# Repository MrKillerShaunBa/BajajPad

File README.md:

# BajajPad

A handy macropad with a rotary encoder and an OLED display. This is created for the Hack Club HackPad V3 YSWS.

### Inspiration

I looked at so many different projects which motivated me to try my hand at this.

### Challenges

I used 3D modelling and PCB software for the first time. It took a lot of time and a lot of Google searches to finally complete it. I faced a lot of problems in Fusion 360 particularly when aligning the case parts, PCB and keycaps for a test fit. 

Schematic            |  PCB         |   Case
:-------------------------:|:-------------------------:|:-------------------------:|
||

## BOM
- 11x Cherry MX Switches
- 1x XIAO RP2040
- 11x Blank DSA Keycaps
- 1x EC11 Rotary Encoder
- 1x 0.91 inch OLED display
- 4x M3x16 Bolt
- 4x M3 Heatset
- 1x Knob (if available)

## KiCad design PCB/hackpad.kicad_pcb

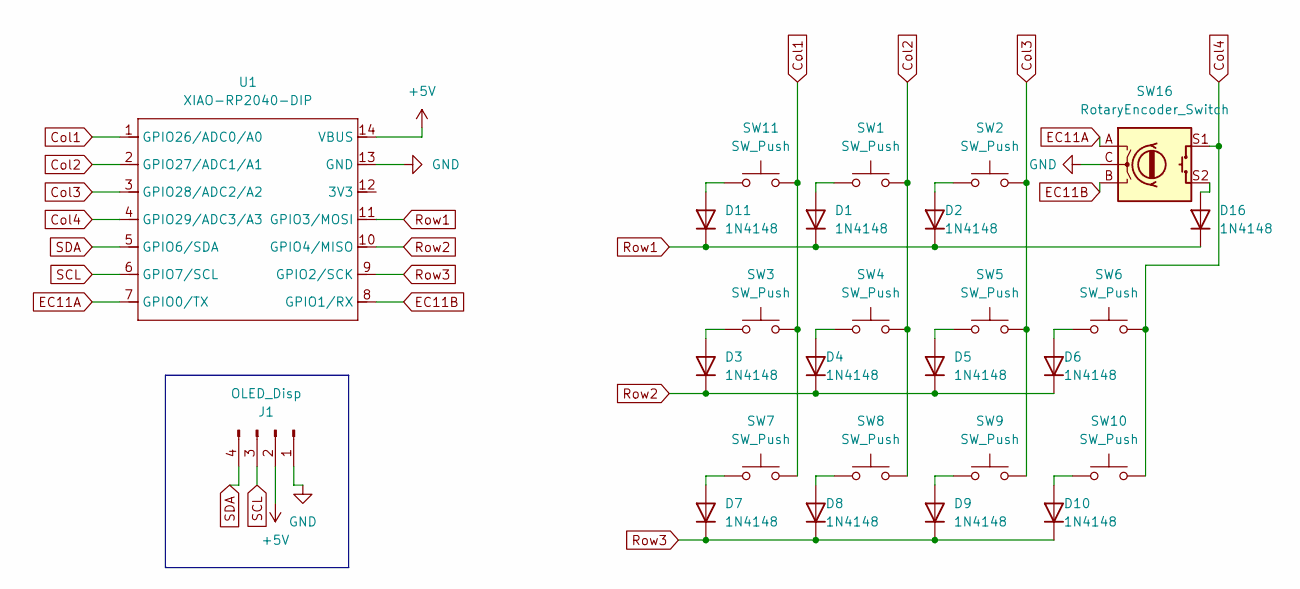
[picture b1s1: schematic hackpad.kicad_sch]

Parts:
D1, D2, D3, D4, D5, D6, D7, D8, D9, D10, D11, D16: 1N4148; D_DO-35_SOD27_P7.62mm_Horizontal
J1: OLED_Disp; SSD1306-0.91-OLED-4pin-128x32_3d
SW1, SW2, SW3, SW4, SW5, SW6, SW7, SW8, SW9, SW10, SW11: SW_Push; SW_Cherry_MX_1.00u_PCB_3D
SW16: RotaryEncoder_Switch; RotaryEncoder_Alps_EC11E-Switch_Vertical_H20mm_3d
U1: XIAO-RP2040-DIP; XIAO-RP2040-DIP_3d

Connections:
+5V: J1.2, U1.14 (VBUS)
Col1: SW3.2, SW7.2, SW11.2, U1.1 (GPIO26/ADC0/A0)
Col2: SW1.2, SW4.2, SW8.2, U1.2 (GPIO27/ADC1/A1)
Col3: SW2.2, SW5.2, SW9.2, U1.3 (GPIO28/ADC2/A2)
Col4: SW6.2, SW10.2, SW16.S1, U1.4 (GPIO29/ADC3/A3)
EC11A: SW16.A, U1.7 (GPIO0/TX)
EC11B: SW16.B, U1.8 (GPIO1/RX)
GND: J1.1, SW16.C, U1.13 (GND)
unnamed: D1.2 (A), SW1.1
unnamed: D2.2 (A), SW2.1
unnamed: D3.2 (A), SW3.1
unnamed: D4.2 (A), SW4.1
unnamed: D5.2 (A), SW5.1
unnamed: D6.2 (A), SW6.1
unnamed: D7.2 (A), SW7.1
unnamed: D8.2 (A), SW8.1
unnamed: D9.2 (A), SW9.1
unnamed: D10.2 (A), SW10.1
unnamed: D11.2 (A), SW11.1
unnamed: D16.2 (A), SW16.S2
Row1: D1.1 (K), D2.1 (K), D11.1 (K), D16.1 (K), U1.11 (GPIO3/MOSI)
Row2: D3.1 (K), D4.1 (K), D5.1 (K), D6.1 (K), U1.10 (GPIO4/MISO)
Row3: D7.1 (K), D8.1 (K), D9.1 (K), D10.1 (K), U1.9 (GPIO2/SCK)
SCL: J1.3, U1.6 (GPIO7/SCL)
SDA: J1.4, U1.5 (GPIO6/SDA)

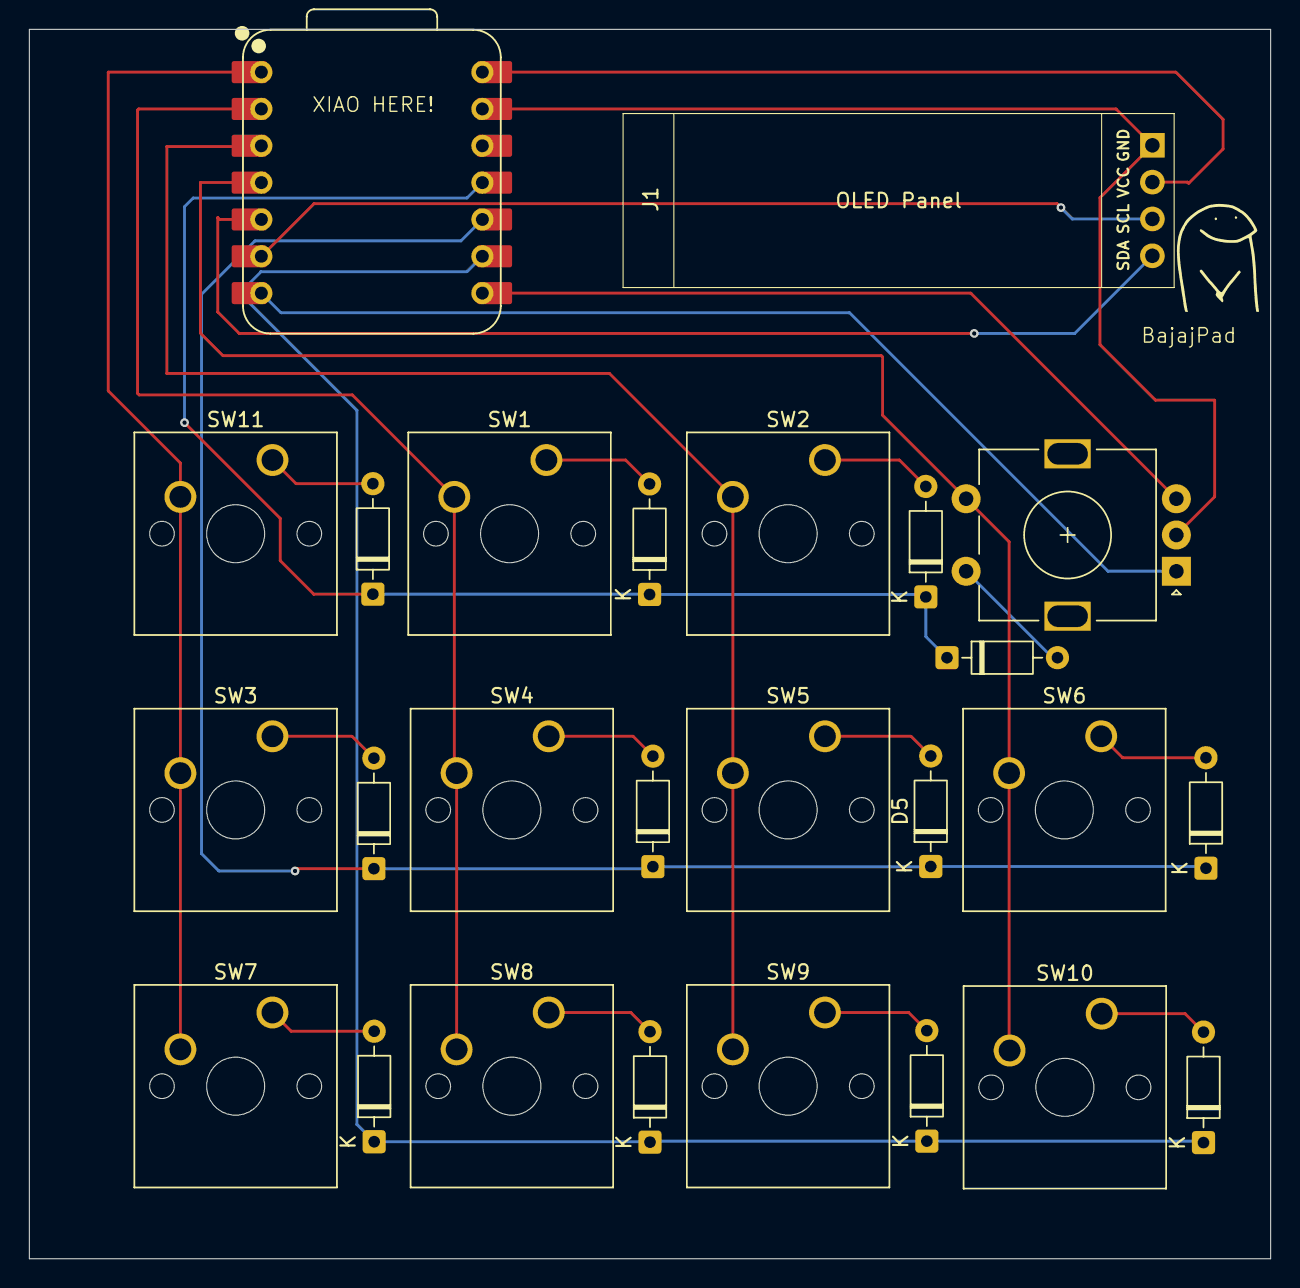
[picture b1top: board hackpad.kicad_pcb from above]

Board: 2 copper layers, 85.6 x 84.8 mm, 26 parts (0 on the bottom side), 25 nets.

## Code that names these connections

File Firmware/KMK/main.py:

import board
import busio

import asyncio
from kmk.kmk_keyboard import KMKKeyboard
from kmk.scanners.keypad import KeysScanner
from kmk.scanners import DiodeOrientation
from kmk.keys import KC
from kmk.modules.macros import Macros
from kmk.extensions.display import Display, TextEntry, BitmapEntry
from kmk.handlers.sequences import simple_key_sequence, send_string
from kmk.extensions.display.ssd1306 import SSD1306
from kmk.modules.encoder import EncoderHandler
import time

last_encoder_event_time = 0
display_timeout = 2

COL1 = board.GP26
COL2 = board.GP27
COL3 = board.GP28
COL4 = board.GP29
ROW1 = board.GP3
ROW2 = board.GP4
ROW3 = board.GP2

bus = busio.I2C(board.GP_SCL, board.GP_SDA)
driver = SSD1306(i2c=bus, device_address=0x3C)

display = Display(
    display=driver,
    flip=True,
    width=128,
    height=32,
    dim_time=10,
    dim_target=0.2,
    off_time=1200,
    brightness=0.8
)
default_display = [
    TextEntry(text='BajajPad', x=64, y=12, x_anchor="M"),
]
display.entries = default_display

keyboard = KMKKeyboard()
encoder_handler = EncoderHandler()

macros = Macros()
keyboard.modules.append(macros)
keyboard.modules.append(encoder_handler)
keyboard.extensions.append(display)

keyboard.col_pins = (COL1, COL2, COL3, COL4)
keyboard.row_pins = (ROW1, ROW2, ROW3)
keyboard.diode_orientation = DiodeOrientation.COL2ROW

encoder_handler.pins =((board.GP0,board.GP1),)
encoder_handler.map = [(KC.VOLD, KC.VOLU)]

rick_art = [
    0b0000011110000000,
    0b0001111111100000,
    0b0011111111110000,
    0b0111101111011000,
    0b0111111111111000,
    0b0111111111111000,
    0b0011011110110000,
    0b0000111111000000,
    0b0000111111000000,
    0b0000111111000000,
    0b0000110111000000,
    0b0000010010000000,
    0b0000010010000000,
    0b0000110111000000,
    0b0000011110000000,
    0b0000000000000000,
]
def show_rickroll_animation():
    display.display_image([
        BitmapEntry(bitmap=rick_art, width=16, height=16, x=56, y=8),
    ])
async def rickroll_action(*args, **kwargs):
    show_rickroll_animation()
    keyboard.tap_key([KC.LGUI, KC.R])
    keyboard.send_string("https://www.youtube.com/watch?v=dQw4w9WgXcQ\n")
    await asyncio.sleep(3)
    display.entries = default_display

def show_volume_change(text):
    display.entries = [
        TextEntry(text=text, x=64, y=12, x_anchor="M")
    ]
def handle_encoder(index, direction):
    global last_encoder_event_time

    if direction > 0:
        keyboard.send(KC.VOLU)
        show_volume_change("Volume UP ↑")
    elif direction < 0:
        keyboard.send(KC.VOLD)
        show_volume_change("Volume DOWN ↓")

    last_encoder_event_time = time.monotonic()

encoder_handler.handlers = [handle_encoder]

rickroll_macro = rickroll_action
ss_macro = simple_key_sequence((KC.LGUI, KC.LSHIFT, KC.S))
keyboard.keymap = [
    [[KC.LALT, KC.TAB], KC.W,               ss_macro,           KC.MUTE],
    [KC.A,              KC.S,               KC.D,               [KC.LGUI, KC.L]],
    [[KC.LCTRL, KC.C],  [KC.LCTRL, KC.V],   [KC.LCTRL, KC.X],   rickroll_macro],
]
idle_display = [TextEntry(text='BajajPad', x=64, y=12, x_anchor="M")]
display.entries = idle_display

if __name__ == '__main__':
    keyboard.go()
    if (time.monotonic() - last_encoder_event_time > display_timeout and display.entries != idle_display):
            display.entries = idle_display

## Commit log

2025-07-03 Added necessary files
2025-07-03 Rename Screenshot 2025-07-04 025749.png to PCB.png
2025-07-03 Rename temp.md to temp.md
2025-07-03 Rename PCB.png to PCB.png
2025-07-03 Rename Screenshot 2025-07-04 025842.png to Schematic
2025-07-03 Rename Schematic to Schematic.png
2025-07-03 Rename Screenshot 2025-07-03 025342.png to overall.png
2025-07-03 Rename poto.png to no_bg.png
2025-07-03 Rename Screenshot 2025-07-04 033717.png to case.png
